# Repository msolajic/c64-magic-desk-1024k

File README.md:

# c64-magic-desk-1024k
Hardware design of Magic Desk compatible C64 cartridge up to 1024k

This is the hardware part that accompanies the project of [Magic Desk Cartridge Generator](https://bitbucket.org/zzarko/magic-desk-cartridge-generator/)

You can order these PCBs on [PCBWay](https://pcbway.com/g/YFnBAc) and help with further C64 hardware developments!

Hardware Description
--------------------

Magic Desk cartridges, in their original form, could hold up to 128Kb of code, or up to 16 banks of 8Kb each. Bank selection is done by writing to $DE00. If bit 8 is set, then EXROM is disabled and RAM in the range of $8000 - $9FFF is usable.

This cartridge expands on the idea by having 128 banks of 8Kb available, thus the maximum size is 1 Mb.

Inputs of an 8-bit latch (74LS273) are connected to the data lines. Correct decoding for the I/O1 signal is done by combining PHI2 and I/O1 trough the NOR gates of 74LS02. The only feature that is deviant from the original Magic Desk specification, is that when you disable the cartridge by writing a value of $80 or larger to $DE00, the banking mechanism gets locked and no more write attempts to $DE00 will change the register's state until a hardware reset is performed. This had to be done because some programs would unintentionally write to $DE00 (or any other location in the I/O1 range) and sometimes, if $01 is wrongly set by the program, it could result in a crash. Since the use of this particular cartrige is primarily to enable making onefile program compilations, we have decided to do it this way. If you want (or need) full compatibility with the original Magic Desk cartridge hardware, we have left a jumper to disable this behaviour. Cut the track exposed on the LOCK / NO LOCK jumper on the bottom side of the cartridge PCB, and connect it the other way around. This way the locking mechanism is disabled, but still you can remove the cartridge from the memory map by setting the bit 7 of the latch high.

The PCB was designed to accomodate various types of EPROMs and their FLASH variants. The smallest EPROM you can use is 27C010 (128Kb), and the largest is 27C040 (512 Kb). You can install two 27C040 (or 29F040) to achieve a full megabyte. Note that you cannot install two EPROMs smaller than 27C040, because there will be a "hole" in the memory space.

Jumper configuration
--------------------

In order to support all possible types of EPROMs and FLASH EPROMs, two solder jumpers had to be placed on the right side of the PCB. They look like this:

```
  PIN1         PIN31
[X X-X]       [X X-X]      
```

These jumpers are preconfigured for 29F040 FLASH EPROMs. Different types of EPROMs and their FLASH variants have some pins swapped, and if you are using a chip smaller than the maximum size, the unused adress lines have to be pulled high on the EPROM side to ensure proper functioning. The function of the jumpers are connected according to the table:

| Jumper | Pin | Description                                      |
|--------|-----|--------------------------------------------------|
| PIN1   | 1   | routes either A18 or VCC to pin 1 of BOTH EPROMs |
| PIN31  | 31  | routes either A18 or VCC to pin 31 of BOTH EPROM |

Here is the table for configuring the jumpers on most common variants of EPROMS and their FLASH counterparts.

# WARNING-THE TABLE IS NOT YET CORRECT!

```
       27C010    29F010     27C020     29F020     27C040     29F040
       ------    ------     ------     ------     ------     ------

PIN1  [X X=X]    [X X X]    [X X=X]    [X X=X]    [X X=X]    [X=X X]
PIN31 [X X=X]    [X X=X]    [X X=X]    [X X=X]    [X=X X]    [X X=X]
```

Precautions have been taken to ensure the corectness of the table above. Please, check the datasheet of your particular (FLASH) EPROM and configure the jumpers accordingly.

RESET button
------------

The pads for the RESET button will accomodate both vertical and horizontal miniature tact switch, and the two pads are there to help you to run a wire for a switch if you are putting the PCB in a cartridge case.

Enclosure compatibility
-----------------------

The PCB is designed so it can be used in various types of cartridge cases. It has been designed to fit the original Commodore cases and cases from the Polish companies KRADEX / MASZCZYK which are available at some retailers in Europe. It also fits in a 3D-prited case from the model available at Thingiverse. Unfortunately, we don't have all of the cartridge cases available in the market, so the design is NOT tested to fit with: Individual Computers', TFW8B and Shareware Plus' (and all other currently available) cases. If anyone wants to donate these types of cartridge cases, adjustments to the PCB could be made and a "one board fits all" PCB could be produced.
Please note - the cartridge cases from KRADEX / MASZCZYK are "low profile", and you cannot use a socket for the EPROM with this type of cases!

Copyright
---------

Cartridge schematics and PCB design (c) 2013-2019 Marko Šolajić

Released under GNU General Public License v3.0, see LICENSE file.

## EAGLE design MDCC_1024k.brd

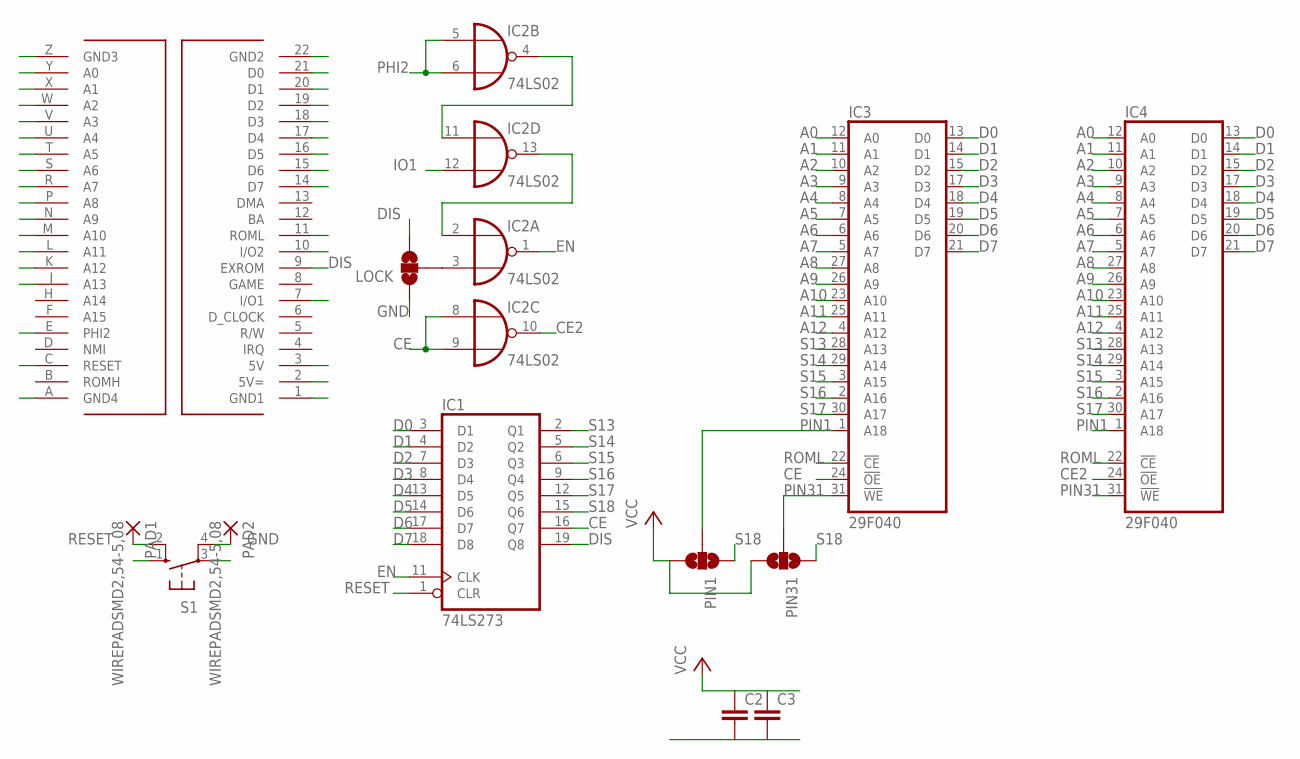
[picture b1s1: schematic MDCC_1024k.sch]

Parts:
C2, C3: C-EU025-024X044; C025-024X044
IC1: 74LS273; DIL20
IC2: 74LS02; DIL14
IC3, IC4: 29F040; DIL32-6
LOCK: SOLDERJUMPER_2WAYS; SJ_3
PAD1, PAD2: WIREPADSMD2,54-5,08; SMD2,54-5,08
PIN1, PIN31: SOLDERJUMPER_2WAYS; SJ_3
S1: 10-XX; B3F-10XX
U$1: C64_EXPANSION__CARTRIDGE

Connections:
A0: IC3.12 (A0), IC4.12 (A0), U$1.Y (A0)
A1: IC3.11 (A1), IC4.11 (A1), U$1.X (A1)
A2: IC3.10 (A2), IC4.10 (A2), U$1.W (A2)
A3: IC3.9 (A3), IC4.9 (A3), U$1.V (A3)
A4: IC3.8 (A4), IC4.8 (A4), U$1.U (A4)
A5: IC3.7 (A5), IC4.7 (A5), U$1.T (A5)
A6: IC3.6 (A6), IC4.6 (A6), U$1.S (A6)
A7: IC3.5 (A7), IC4.5 (A7), U$1.R (A7)
A8: IC3.27 (A8), IC4.27 (A8), U$1.P (A8)
A9: IC3.26 (A9), IC4.26 (A9), U$1.N (A9)
A10: IC3.23 (A10), IC4.23 (A10), U$1.M (A10)
A11: IC3.25 (A11), IC4.25 (A11), U$1.L (A11)
A12: IC3.4 (A12), IC4.4 (A12), U$1.K (A12)
A13: U$1.J (A13)
CE: IC1.16 (Q7), IC2.8 (I0), IC2.9 (I1), IC3.24 (!OE)
CE2: IC2.10 (O), IC4.24 (!OE)
D0: IC1.3 (D1), IC3.13 (D0), IC4.13 (D0), U$1.21 (D0)
D1: IC1.4 (D2), IC3.14 (D1), IC4.14 (D1), U$1.20 (D1)
D2: IC1.7 (D3), IC3.15 (D2), IC4.15 (D2), U$1.19 (D2)
D3: IC1.8 (D4), IC3.17 (D3), IC4.17 (D3), U$1.18 (D3)
D4: IC1.13 (D5), IC3.18 (D4), IC4.18 (D4), U$1.17 (D4)
D5: IC1.14 (D6), IC3.19 (D5), IC4.19 (D5), U$1.16 (D5)
D6: IC1.17 (D7), IC3.20 (D6), IC4.20 (D6), U$1.15 (D6)
D7: IC1.18 (D8), IC3.21 (D7), IC4.21 (D7), U$1.14 (D7)
DIS: IC1.19 (Q8), LOCK.3, U$1.9 (EXROM)
EN: IC1.11 (CLK), IC2.1 (O)
GND: C2.2, C3.2, IC1.10 (GND), IC2.7 (GND), IC3.16 (GND), IC4.16 (GND), LOCK.1, PAD2.1, S1.3, S1.4 (P1), U$1.1 (GND1), U$1.22 (GND2), U$1.A (GND4), U$1.Z (GND3)
IO1: IC2.12 (I1), U$1.7 (I/O1)
IO2: U$1.10 (I/O2)
unnamed: IC2.3 (I1), LOCK.2
unnamed: IC2.4 (O), IC2.11 (I0)
unnamed: IC2.2 (I0), IC2.13 (O)
PHI2: IC2.5 (I0), IC2.6 (I1), U$1.E (PHI2)
PIN1: IC3.1 (A18), IC4.1 (A18), PIN1.2
PIN31: IC3.31 (!WE), IC4.31 (!WE), PIN31.2
RESET: IC1.1 (CLR), PAD1.1, S1.1 (S), S1.2 (S1), U$1.C (RESET)
ROML: IC3.22 (!CE), IC4.22 (!CE), U$1.11 (ROML)
S13: IC1.2 (Q1), IC3.28 (A13), IC4.28 (A13)
S14: IC1.5 (Q2), IC3.29 (A14), IC4.29 (A14)
S15: IC1.6 (Q3), IC3.3 (A15), IC4.3 (A15)
S16: IC1.9 (Q4), IC3.2 (A16), IC4.2 (A16)
S17: IC1.12 (Q5), IC3.30 (A17), IC4.30 (A17)
S18: IC1.15 (Q6), PIN1.1, PIN31.1
VCC: C2.1, C3.1, IC1.20 (VCC), IC2.14 (VCC), IC3.32 (VCC), IC4.32 (VCC), PIN1.3, PIN31.3, U$1.2 (5V=), U$1.3 (5V)

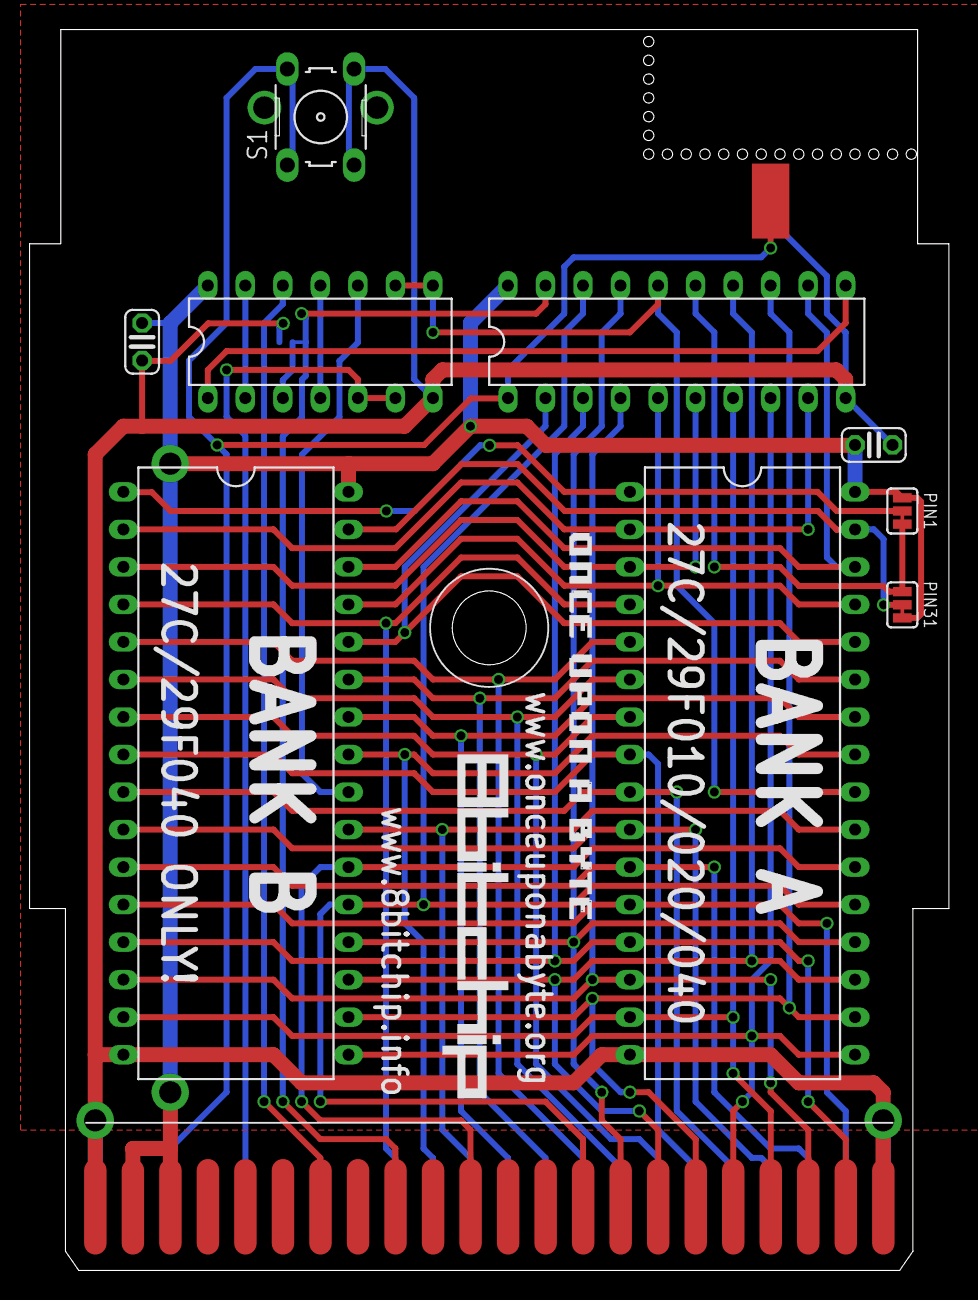
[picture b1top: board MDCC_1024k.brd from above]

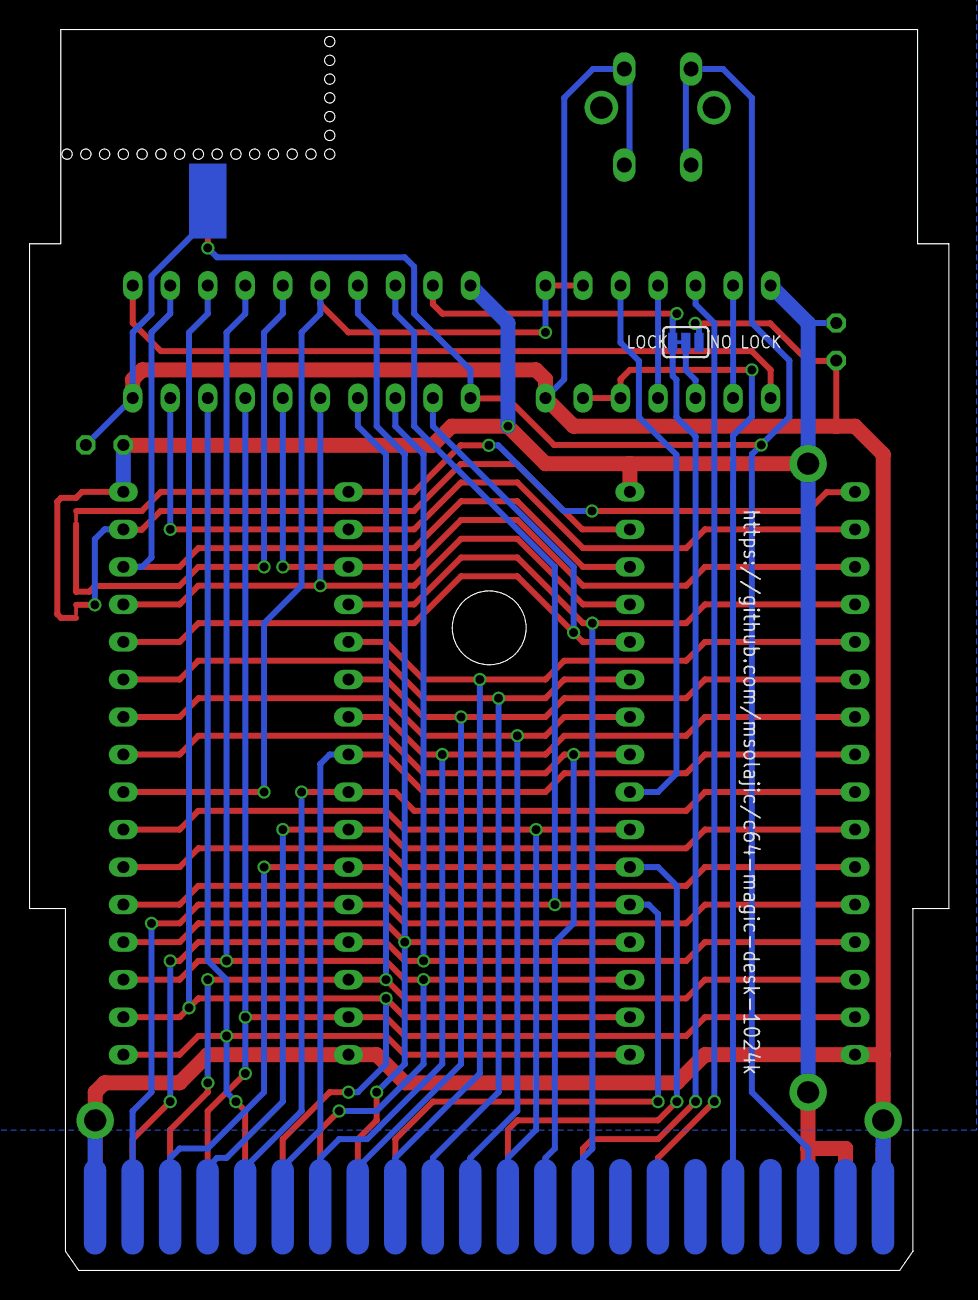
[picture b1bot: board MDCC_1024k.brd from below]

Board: 2 copper layers, 62.2 x 84.0 mm, 13 parts (2 on the bottom side), 42 nets.

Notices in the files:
parts and their libraries:
SparkFun-Passives: Licensing: Creative Commons ShareAlike 4.0 International - https://creativecommons.org/licenses/by-sa/4.0
